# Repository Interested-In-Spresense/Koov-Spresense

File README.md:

# SpresenseでKOOVを動かすプロジェクト！

使わなくなってしまった子供たちのKOOVキットをSpresense(Arduino)で動かして、活用しようとするプロジェクト。<br>
下記の免責事項にご了承の方であれば、商業利用も含み自由にお使いくださって構いません。

## 免責事項

本リポジトリに含まれるコードおよび回路図は、個人的な学習・研究目的で提供されており、商用利用を目的としていません。
これらの内容は、正確性、信頼性、または動作保証について一切の保証を行いません。使用者は、自己の責任において本リポジトリのコードおよび回路図を使用するものとします。

### 注意事項

- 本リポジトリに含まれる回路図やコードの動作は、環境や実装条件によって異なる場合があります。使用前に十分なテストを行ってください。
- 万が一、使用に起因する損害や問題が発生した場合、リポジトリの管理者は一切の責任を負いません。

## ライセンス

本コードおよび回路図は、Creative Commons CC0 1.0 Public Domain Dedication)ライセンスの下で公開されています。

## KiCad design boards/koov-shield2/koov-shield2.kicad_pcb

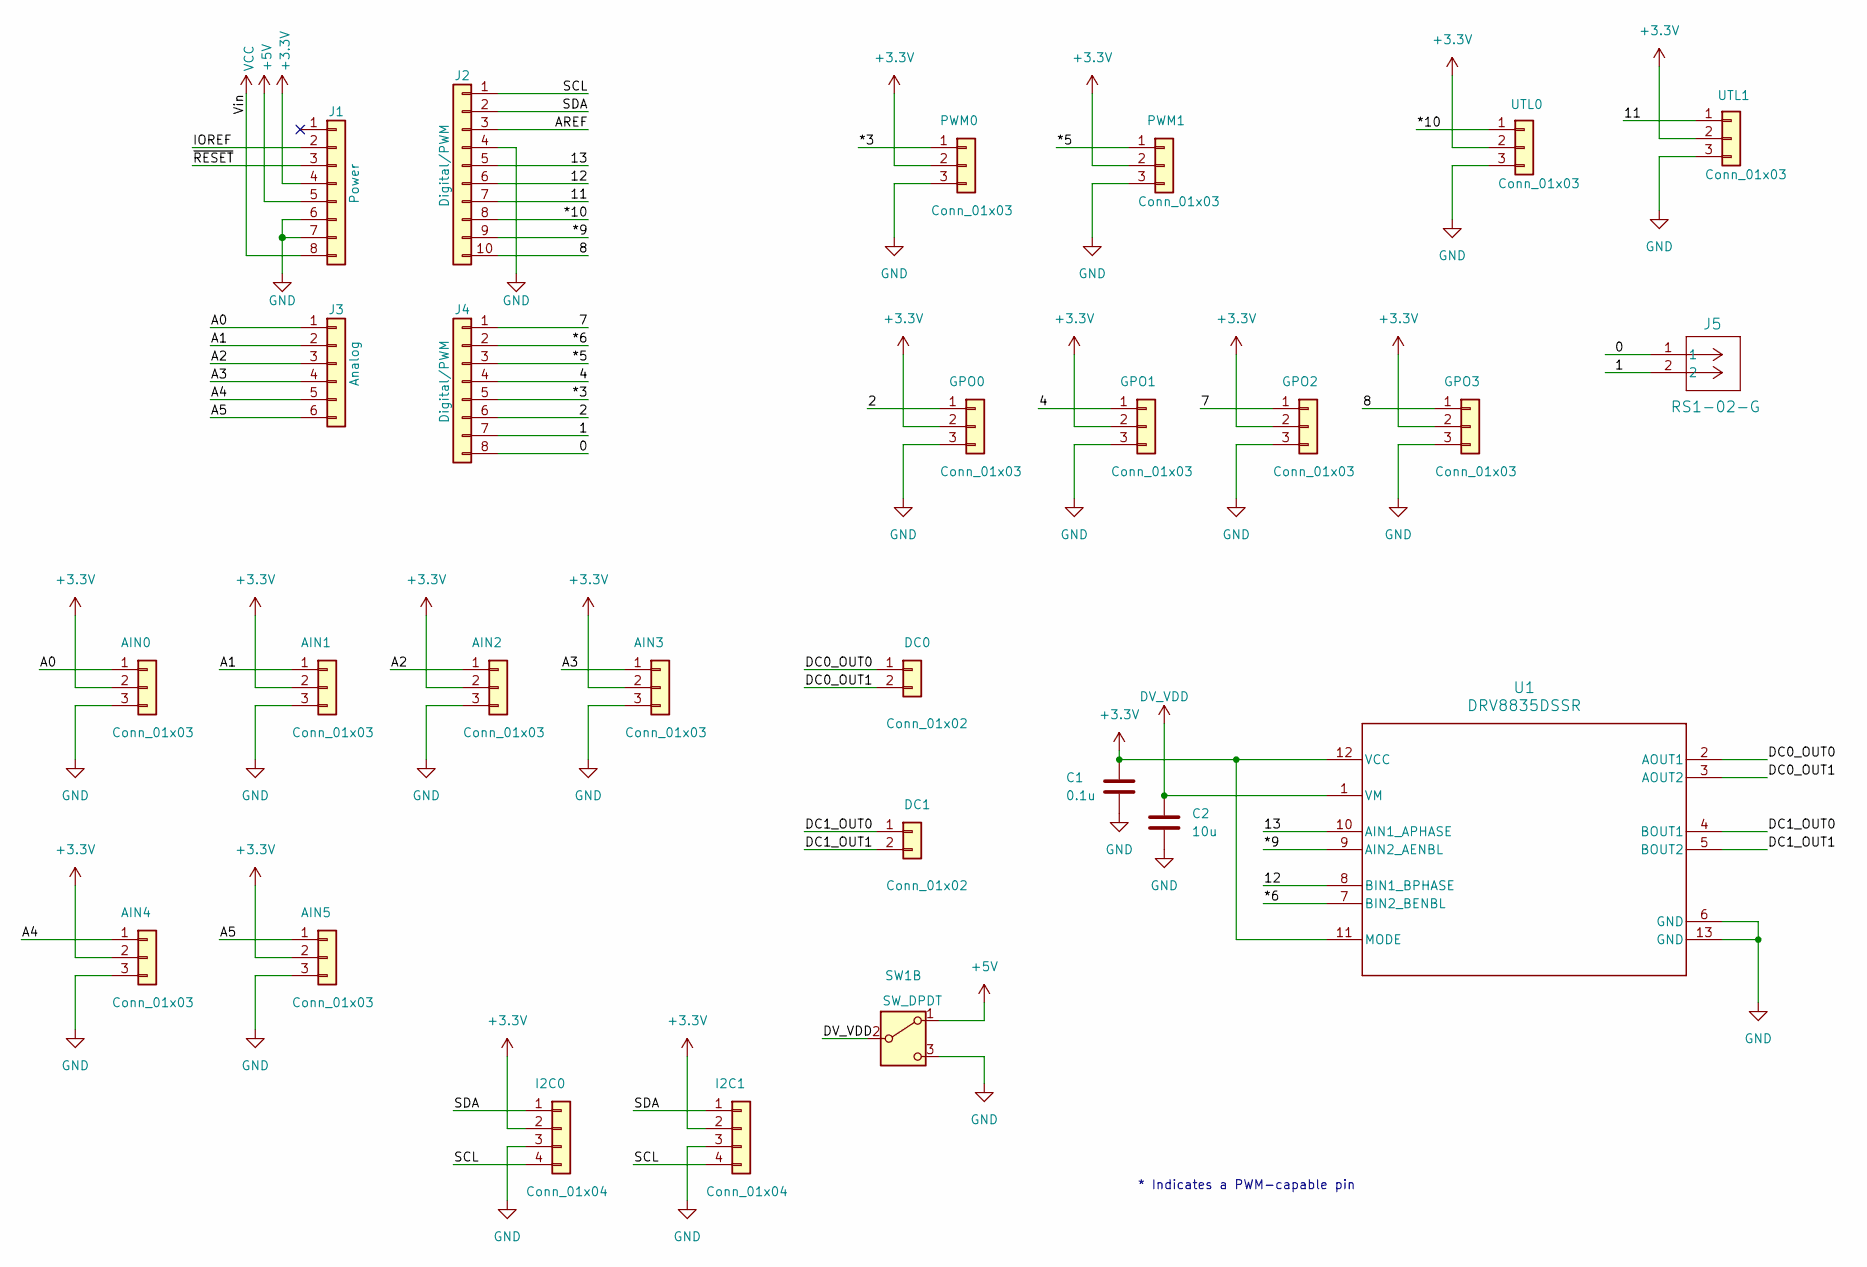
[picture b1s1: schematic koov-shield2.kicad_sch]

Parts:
AIN0, AIN1, AIN2, AIN3, AIN4, AIN5: Conn_01x03; PinHeader_1x03_P2.54mm_Vertical
C1: 0.1u; C_0402_1005Metric_Pad0.74x0.62mm_HandSolder
C2: 10u; C_0603_1608Metric_Pad1.08x0.95mm_HandSolder
DC0, DC1: Conn_01x02; PinHeader_1x02_P2.54mm_Vertical
GPO0, GPO1, GPO2, GPO3: Conn_01x03; PinHeader_1x03_P2.54mm_Vertical
I2C0, I2C1: Conn_01x04; PinHeader_1x04_P2.54mm_Vertical
J1: Power; PinHeader_1x08_P2.54mm_Vertical
J2: Digital/PWM; PinHeader_1x10_P2.54mm_Vertical
J3: Analog; PinHeader_1x06_P2.54mm_Vertical
J4: Digital/PWM; PinHeader_1x08_P2.54mm_Vertical
J5: RS1-02-G; CONN_RS1-02-G_ADM
PWM0, PWM1: Conn_01x03; PinHeader_1x03_P2.54mm_Vertical
SW1: SW_DPDT; AKIZUKI-SS-12D00G3
U1: DRV8835DSSR; DSS0012A
UTL0, UTL1: Conn_01x03; PinHeader_1x03_P2.54mm_Vertical

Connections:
+3.3V: AIN0.2, AIN1.2, AIN2.2, AIN3.2, AIN4.2, AIN5.2, C1.1, GPO0.2, GPO1.2, GPO2.2, GPO3.2, I2C0.2, I2C1.2, J1.4, PWM0.2, PWM1.2, U1.11 (MODE), U1.12 (VCC), UTL0.2, UTL1.2
+5V: J1.5, SW1.1 (A)
/0: J4.8, J5.1
/1: J4.7, J5.2
/2: GPO0.1, J4.6
/4: GPO1.1, J4.4
/7: GPO2.1, J4.1
/8: GPO3.1, J2.10
/11: J2.7, UTL1.1
/12: J2.6, U1.8 (BIN1_BPHASE)
/13: J2.5, U1.10 (AIN1_APHASE)
/*3: J4.5, PWM0.1
/*5: J4.3, PWM1.1
/*6: J4.2, U1.7 (BIN2_BENBL)
/*9: J2.9, U1.9 (AIN2_AENBL)
/*10: J2.8, UTL0.1
/A0: AIN0.1, J3.1
/A1: AIN1.1, J3.2
/A2: AIN2.1, J3.3
/A3: AIN3.1, J3.4
/A4: AIN4.1, J3.5
/A5: AIN5.1, J3.6
/AREF: J2.3
/DC0_OUT0: DC0.1, U1.2 (AOUT1)
/DC0_OUT1: DC0.2, U1.3 (AOUT2)
/DC1_OUT0: DC1.1, U1.4 (BOUT1)
/DC1_OUT1: DC1.2, U1.5 (BOUT2)
/DV_VDD: C2.1, SW1.2 (B), U1.1 (VM)
/IOREF: J1.2
/SCL: I2C0.4, I2C1.4, J2.1
/SDA: I2C0.1, I2C1.1, J2.2
/~RESET: J1.3
GND: AIN0.3, AIN1.3, AIN2.3, AIN3.3, AIN4.3, AIN5.3, C1.2, C2.2, GPO0.3, GPO1.3, GPO2.3, GPO3.3, I2C0.3, I2C1.3, J1.6, J1.7, J2.4, PWM0.3, PWM1.3, SW1.3 (C), U1.6 (GND), U1.13 (GND), UTL0.3, UTL1.3
VCC: J1.8

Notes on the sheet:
* Indicates a PWM-capable pin

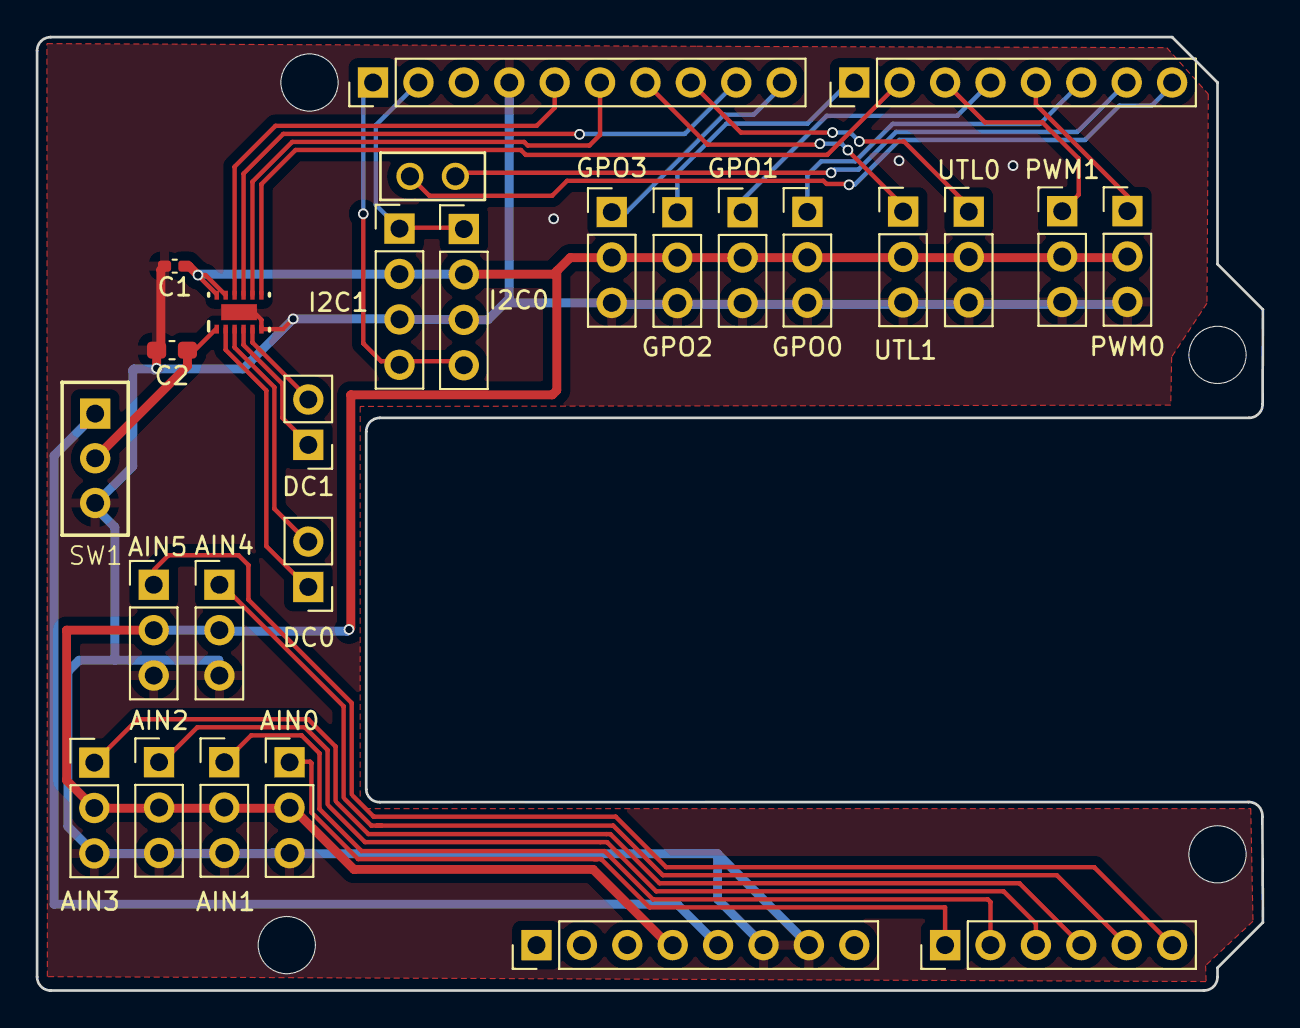
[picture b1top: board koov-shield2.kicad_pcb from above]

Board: 2 copper layers, 68.6 x 53.3 mm, 31 parts (0 on the bottom side), 30 nets.

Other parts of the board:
MH1, MH2, MH3, MH4: MountingHole_3.2mm

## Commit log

2025-02-09 Add board design.
2025-02-21 Correct DC motor connector position.
2025-03-11 Support reverse-insertion-proof.
2025-03-11 Add a circuit that is designed for reflow soldering.
2025-03-12 Wiring UARTs to the unused connector.
2025-04-16 fix swirch miss.
